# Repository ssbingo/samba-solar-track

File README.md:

# Samba Solar Track

**© Silvio Sternitzke, 10/2026** · Lizenz CC BY-NC-SA 4.0 (keine kommerzielle Verwendung, Nachbau für private
Zwecke erlaubt), siehe [LIZENZ.md](LIZENZ.md)

Samba Solar Track ist eine Solarnachführung mit Sturmschutz für bewegliche Aufständerungen von Solarmodulen:
nur vertikal (1 Achse, Elevation) oder vertikal + horizontal (2 Achsen, Elevation und Azimut). Sie besteht aus
einem gekauften Waveshare ESP32-P4-WIFI6-Touch-LCD-10.1 (10,1-Zoll-Touch-Display) und einer eigenen Platine, die Sensoren, Schaltausgänge und
Meldeleuchten trägt. Dieses Repository enthält ausschließlich, was du für den Nachbau der Steuerung brauchst:
Handbuch, Platinen und Gehäuse.

**Stand: Release 0.7.8** (erzeugt aus dem Projekt am 13.11.2026)

## Inhalt

| Ordner | Inhalt |
|---|---|
| `handbuch/` | Handbuch für Anwender als HTML (Startseite `handbuch/index.html`) und als PDF |
| `hardware/RearCircuitBoard_10/` | Platine zum Waveshare ESP32-P4-WIFI6-Touch-LCD-10.1: KiCad-Projekt, Fertigungsdaten für JLCPCB, Stückliste, Vorschaubilder, Steckerliste |
| `hardware/HallTapBoard/` | kleine Platine für den Abgriff der Hall-Signale an der Synchronsteuerung, mit Gehäuse zum 3D-Druck |
| `gehaeuse/` | Rückgehäuse und Bohrschablone für das 10,1-Zoll-Board (STL, 3MF, PDF) |

## Firmware

Die Firmware gibt es nur fertig kompiliert. Die Steuerung holt neue Versionen selbst über das Internet
(Einrichtung → FIRMWARE); die Dateien für das erste Aufspielen liegen unter <https://firmware.samba-solar.de/>
(Repository [ssbingo/samba-solar-track-firmware](https://github.com/ssbingo/samba-solar-track-firmware)).
Wie du sie zum ersten Mal aufspielst, steht im Handbuch („Die Firmware zum ersten Mal aufspielen“).

## Lizenz

Platinen, Zeichnungen, Gehäuse, Handbuch und Logo stehen unter **CC BY-NC-SA 4.0**: privater Nachbau erlaubt,
keine kommerzielle Verwendung durch Dritte. Einzelheiten in [LIZENZ.md](LIZENZ.md), Lizenztext in [LICENSE](LICENSE).

---

© Silvio Sternitzke, 10/2026 · Samba Solar Track · Lizenz CC BY-NC-SA 4.0 (keine kommerzielle Verwendung,
Nachbau für private Zwecke erlaubt), siehe [LIZENZ.md](LIZENZ.md)

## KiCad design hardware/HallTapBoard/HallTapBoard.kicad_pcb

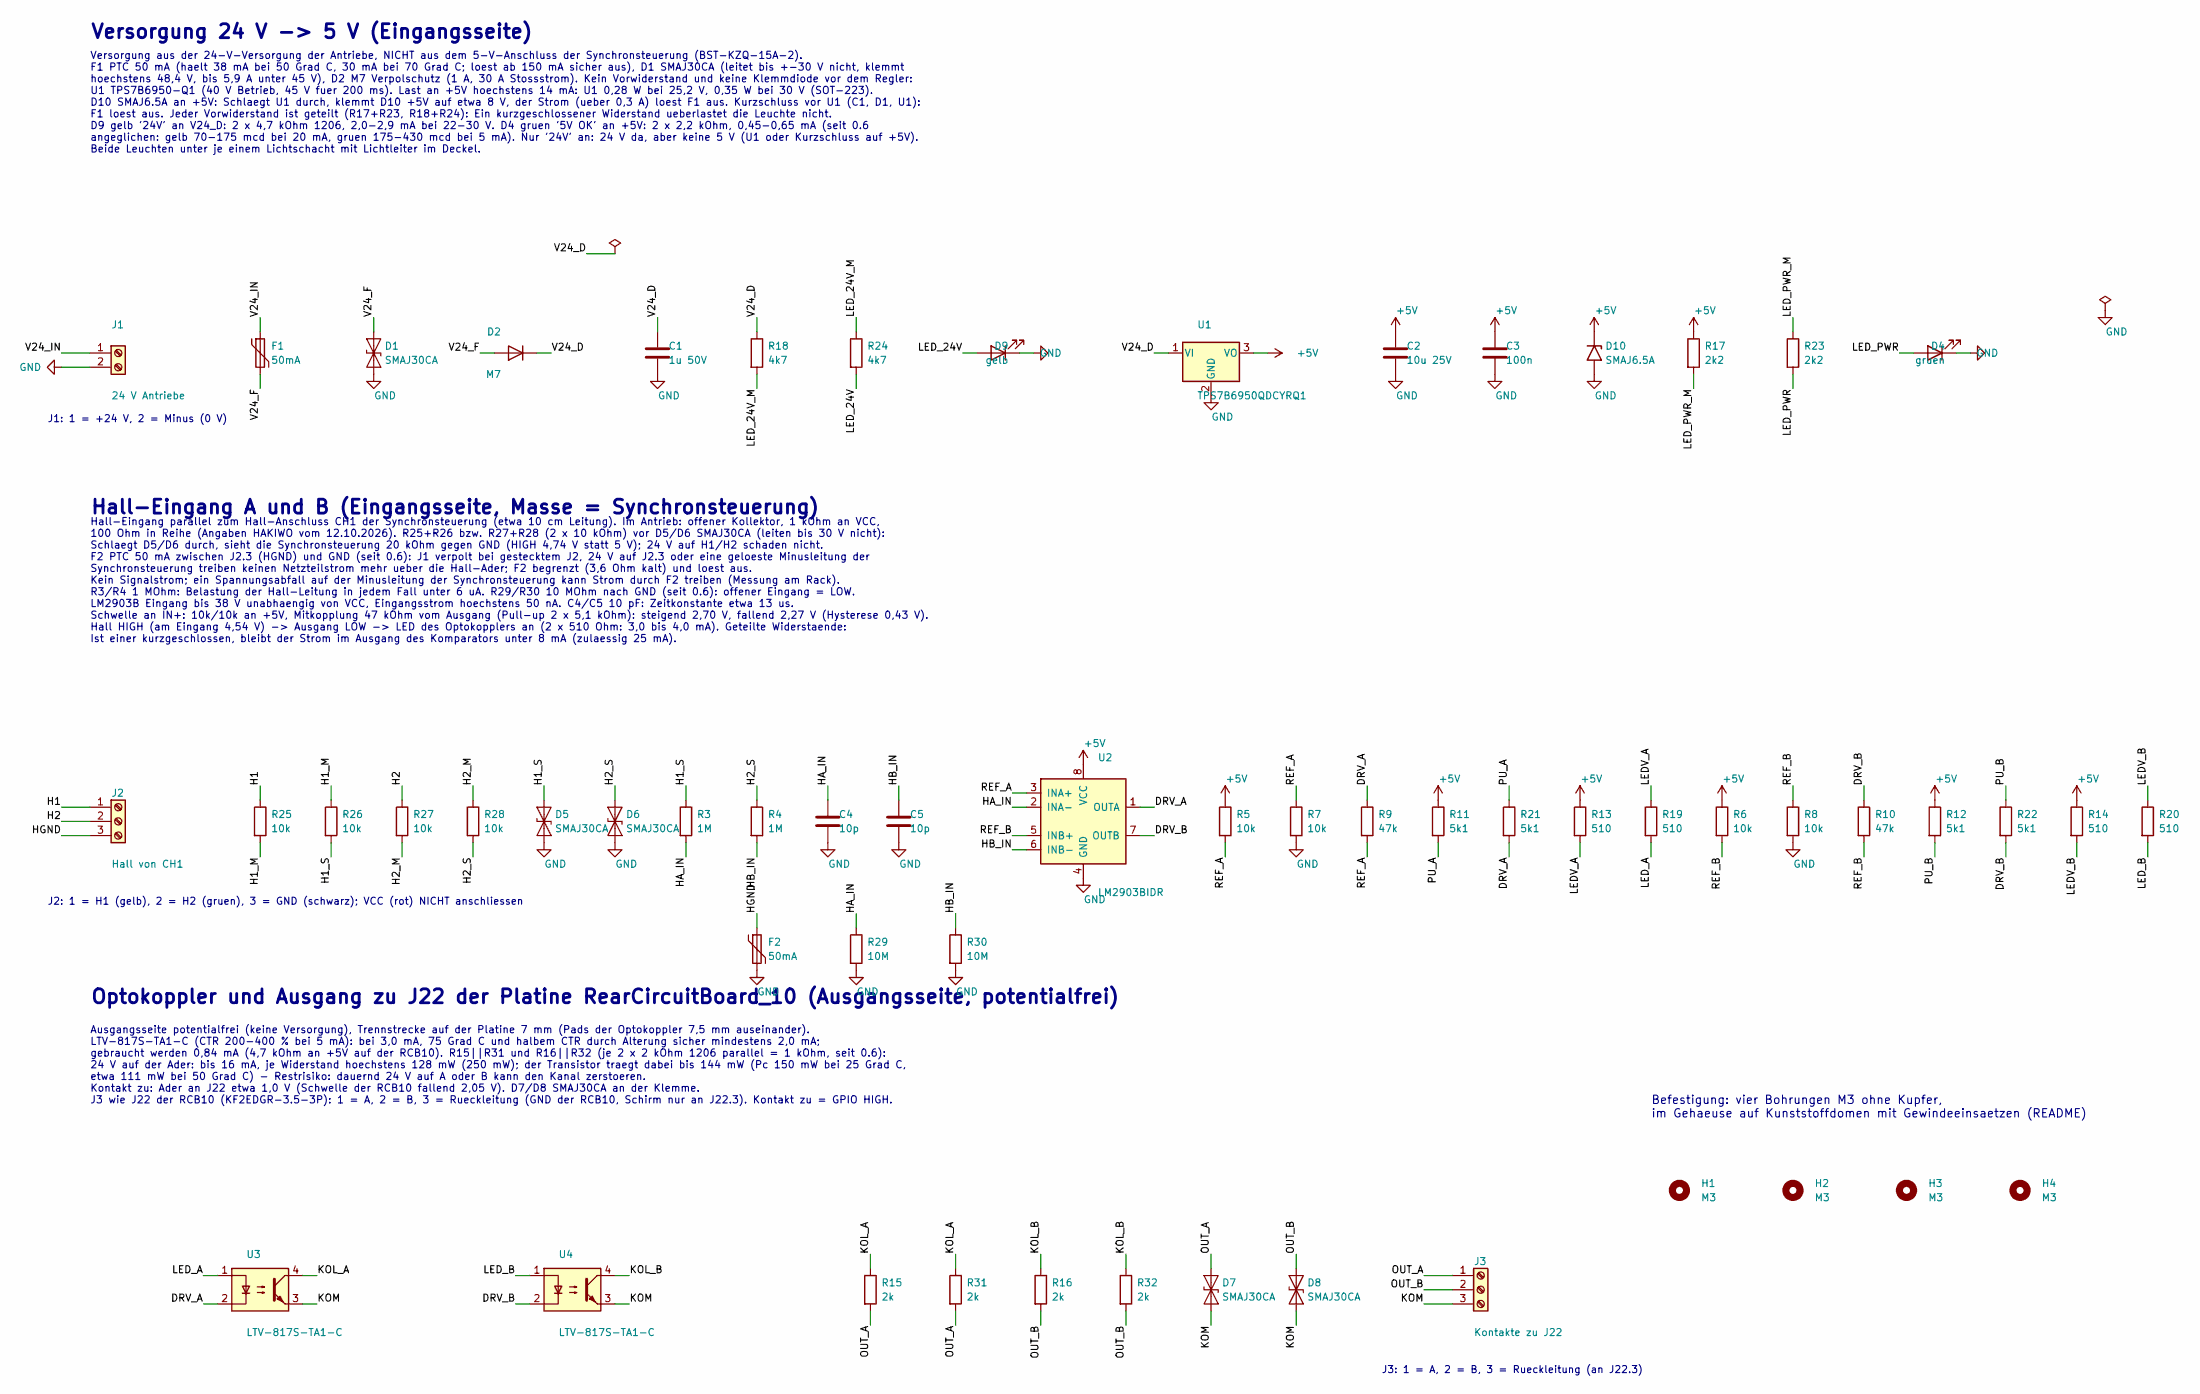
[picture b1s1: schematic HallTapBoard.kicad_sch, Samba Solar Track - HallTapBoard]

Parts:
C1: 1u 50V; C_0805_2012Metric; LCSC C28323
C2: 10u 25V; C_0805_2012Metric; LCSC C15850
C3: 100n; C_0603_1608Metric; LCSC C14663
C4, C5: 10p; C_0603_1608Metric; LCSC C1634
D1, D5, D6, D7, D8: SMAJ30CA; D_SMA; LCSC C110043
D2: M7; D_SMA; LCSC C95872
D4: gruen; LED_0805_2012Metric; LCSC C2297
D9: gelb; LED_0805_2012Metric; LCSC C2296
D10: SMAJ6.5A; D_SMA; LCSC C123817
F1, F2: 50mA; Fuse_1206_3216Metric; LCSC C70064
H1, H2, H3, H4: M3; MountingHole_3.2mm_M3
J1: 24 V Antriebe; Klemme_5.08_2P_KF2EDGRC; LCSC C441236
J2: Hall von CH1; Klemme_3.81_3P_KF2EDGR; LCSC C441183
J3: Kontakte zu J22; Klemme_3.5_3P_KF2EDGR; LCSC C441172
R3, R4: 1M; R_0603_1608Metric; LCSC C22935
R5, R6, R7, R8, R25, R26, R27, R28: 10k; R_0603_1608Metric; LCSC C25804
R9, R10: 47k; R_0603_1608Metric; LCSC C25819
R11, R12, R21, R22: 5k1; R_0603_1608Metric; LCSC C23186
R13, R14, R19, R20: 510; R_0603_1608Metric; LCSC C23193
R15, R16, R31, R32: 2k; R_1206_3216Metric; LCSC C17944
R17, R23: 2k2; R_0603_1608Metric; LCSC C4190
R18, R24: 4k7; R_1206_3216Metric; LCSC C17936
R29, R30: 10M; R_0603_1608Metric; LCSC C7250
U1: TPS7B6950QDCYRQ1; SOT-223-3_TabPin2; LCSC C108469
U2: LM2903BIDR; SOIC-8_3.9x4.9mm_P1.27mm; LCSC C2869804
U3, U4: LTV-817S-TA1-C; SMDIP-4_W9.53mm; LCSC C109227

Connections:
+5V: C2.1, C3.1, D10.1 (A1), R5.1, R6.1, R11.1, R12.1, R13.1, R14.1, R17.1, U1.3 (VO), U2.8 (VCC)
/DRV_A: R9.1, R21.2, U2.1 (OUTA), U3.2
/DRV_B: R10.1, R22.2, U2.7 (OUTB), U4.2
/H1: J2.1, R25.1
/H1_M: R25.2, R26.1
/H1_S: D5.1 (A1), R3.1, R26.2
/H2: J2.2, R27.1
/H2_M: R27.2, R28.1
/H2_S: D6.1 (A1), R4.1, R28.2
/HA_IN: C4.1, R3.2, R29.1, U2.2 (INA-)
/HB_IN: C5.1, R4.2, R30.1, U2.6 (INB-)
/HGND: F2.1, J2.3
/KOL_A: R15.1, R31.1, U3.4
/KOL_B: R16.1, R32.1, U4.4
/KOM: D7.2 (A2), D8.2 (A2), J3.3, U3.3, U4.3
/LEDV_A: R13.2, R19.1
/LEDV_B: R14.2, R20.1
/LED_24V: D9.2 (A), R24.2
/LED_24V_M: R18.2, R24.1
/LED_A: R19.2, U3.1
/LED_B: R20.2, U4.1
/LED_PWR: D4.2 (A), R23.2
/LED_PWR_M: R17.2, R23.1
/OUT_A: D7.1 (A1), J3.1, R15.2, R31.2
/OUT_B: D8.1 (A1), J3.2, R16.2, R32.2
/PU_A: R11.2, R21.1
/PU_B: R12.2, R22.1
/REF_A: R5.2, R7.1, R9.2, U2.3 (INA+)
/REF_B: R6.2, R8.1, R10.2, U2.5 (INB+)
/V24_D: C1.1, D2.1 (K), R18.1, U1.1 (VI)
/V24_F: D1.1 (A1), D2.2 (A), F1.2
/V24_IN: F1.1, J1.1
GND: C1.2, C2.2, C3.2, C4.2, C5.2, D1.2 (A2), D4.1 (K), D5.2 (A2), D6.2 (A2), D9.1 (K), D10.2 (A2), F2.2, J1.2, R7.2, R8.2, R29.2, R30.2, U1.2 (GND), U2.4 (GND)

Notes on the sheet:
Versorgung 24 V -> 5 V (Eingangsseite)
Versorgung aus der 24-V-Versorgung der Antriebe, NICHT aus dem 5-V-Anschluss der Synchronsteuerung (BST-KZQ-15A-2). F1 PTC 50 mA (haelt 38 mA bei 50 Grad C, 30 mA bei 70 Grad C; loest ab 150 mA sicher aus), D1 SMAJ30CA (leitet bis +-30 V nicht, klemmt hoechstens 48,4 V, bis 5,9 A unter 45 V), D2 M7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
J1: 1 = +24 V, 2 = Minus (0 V)
Hall-Eingang A und B (Eingangsseite, Masse = Synchronsteuerung)
Hall-Eingang parallel zum Hall-Anschluss CH1 der Synchronsteuerung (etwa 10 cm Leitung). Im Antrieb: offener Kollektor, 1 kOhm an VCC, 100 Ohm in Reihe (Angaben HAKIWO vom 12.10.2026). R25+R26 bzw. R27+R28 (2 x 10 kOhm) vor D5/D6 SMAJ30CA (leiten bis 30 V nicht): Schlaegt D5/D6 durch, sieht die Syn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
J2: 1 = H1 (gelb), 2 = H2 (gruen), 3 = GND (schwarz); VCC (rot) NICHT anschliessen
Optokoppler und Ausgang zu J22 der Platine RearCircuitBoard_10 (Ausgangsseite, potentialfrei)
Ausgangsseite potentialfrei (keine Versorgung), Trennstrecke auf der Platine 7 mm (Pads der Optokoppler 7,5 mm auseinander). LTV-817S-TA1-C (CTR 200-400 % bei 5 mA): bei 3,0 mA, 75 Grad C und halbem CTR durch Alterung sicher mindestens 2,0 mA; gebraucht werden 0,84 mA (4,7 kOhm an +5V auf der RCB10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
J3: 1 = A, 2 = B, 3 = Rueckleitung (an J22.3)
Befestigung: vier Bohrungen M3 ohne Kupfer, im Gehaeuse auf Kunststoffdomen mit Gewindeeinsaetzen (README)

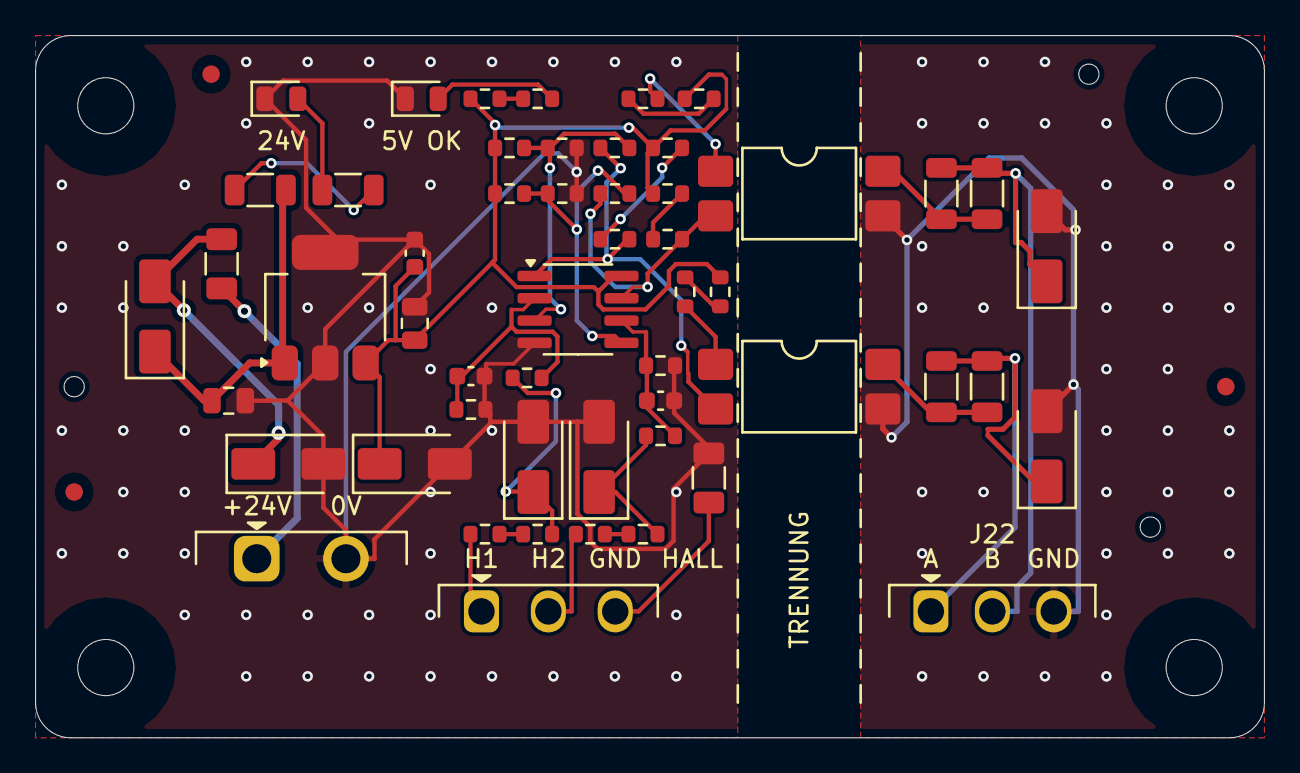
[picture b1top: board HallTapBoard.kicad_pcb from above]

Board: 2 copper layers, 70.0 x 40.0 mm, 63 parts (0 on the bottom side), 33 nets.

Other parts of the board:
FID1, FID2, FID3: Passermarke_1mm
TH1, TH2, TH3: Werkzeugloch_1.152mm

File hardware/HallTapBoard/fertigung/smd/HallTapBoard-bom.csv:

Comment,Designator,Footprint,JLCPCB Part #
1u 50V,C1,C_0805_2012Metric,C28323
10u 25V,C2,C_0805_2012Metric,C15850
100n,C3,C_0603_1608Metric,C14663
10p,"C4,C5",C_0603_1608Metric,C1634
SMAJ30CA,"D1,D5,D6,D7,D8",D_SMA,C110043
M7,D2,D_SMA,C95872
gruen,D4,LED_0805_2012Metric,C2297
gelb,D9,LED_0805_2012Metric,C2296
SMAJ6.5A,D10,D_SMA,C123817
50mA,"F1,F2",Fuse_1206_3216Metric,C70064
1M,"R3,R4",R_0603_1608Metric,C22935
10k,"R5,R6,R7,R8,R25,R26,R27,R28",R_0603_1608Metric,C25804
47k,"R9,R10",R_0603_1608Metric,C25819
5k1,"R11,R12,R21,R22",R_0603_1608Metric,C23186
510,"R13,R14,R19,R20",R_0603_1608Metric,C23193
2k,"R15,R16,R31,R32",R_1206_3216Metric,C17944
2k2,"R17,R23",R_0603_1608Metric,C4190
4k7,"R18,R24",R_1206_3216Metric,C17936
10M,"R29,R30",R_0603_1608Metric,C7250
TPS7B6950QDCYRQ1,U1,SOT-223-3_TabPin2,C108469
LM2903BIDR,U2,SOIC-8_3.9x4.9mm_P1.27mm,C2869804
LTV-817S-TA1-C,"U3,U4",SMDIP-4_W9.53mm,C109227

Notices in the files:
hardware/HallTapBoard/HallTapBoard.kicad_pcb:
Lizenz CC BY-NC-SA 4.0: keine kommerzielle Verwendung, privater Nachbau erlaubt
hardware/HallTapBoard/HallTapBoard.kicad_sch:
Lizenz CC BY-NC-SA 4.0: keine kommerzielle Verwendung durch Dritte, privater Nachbau erlaubt
